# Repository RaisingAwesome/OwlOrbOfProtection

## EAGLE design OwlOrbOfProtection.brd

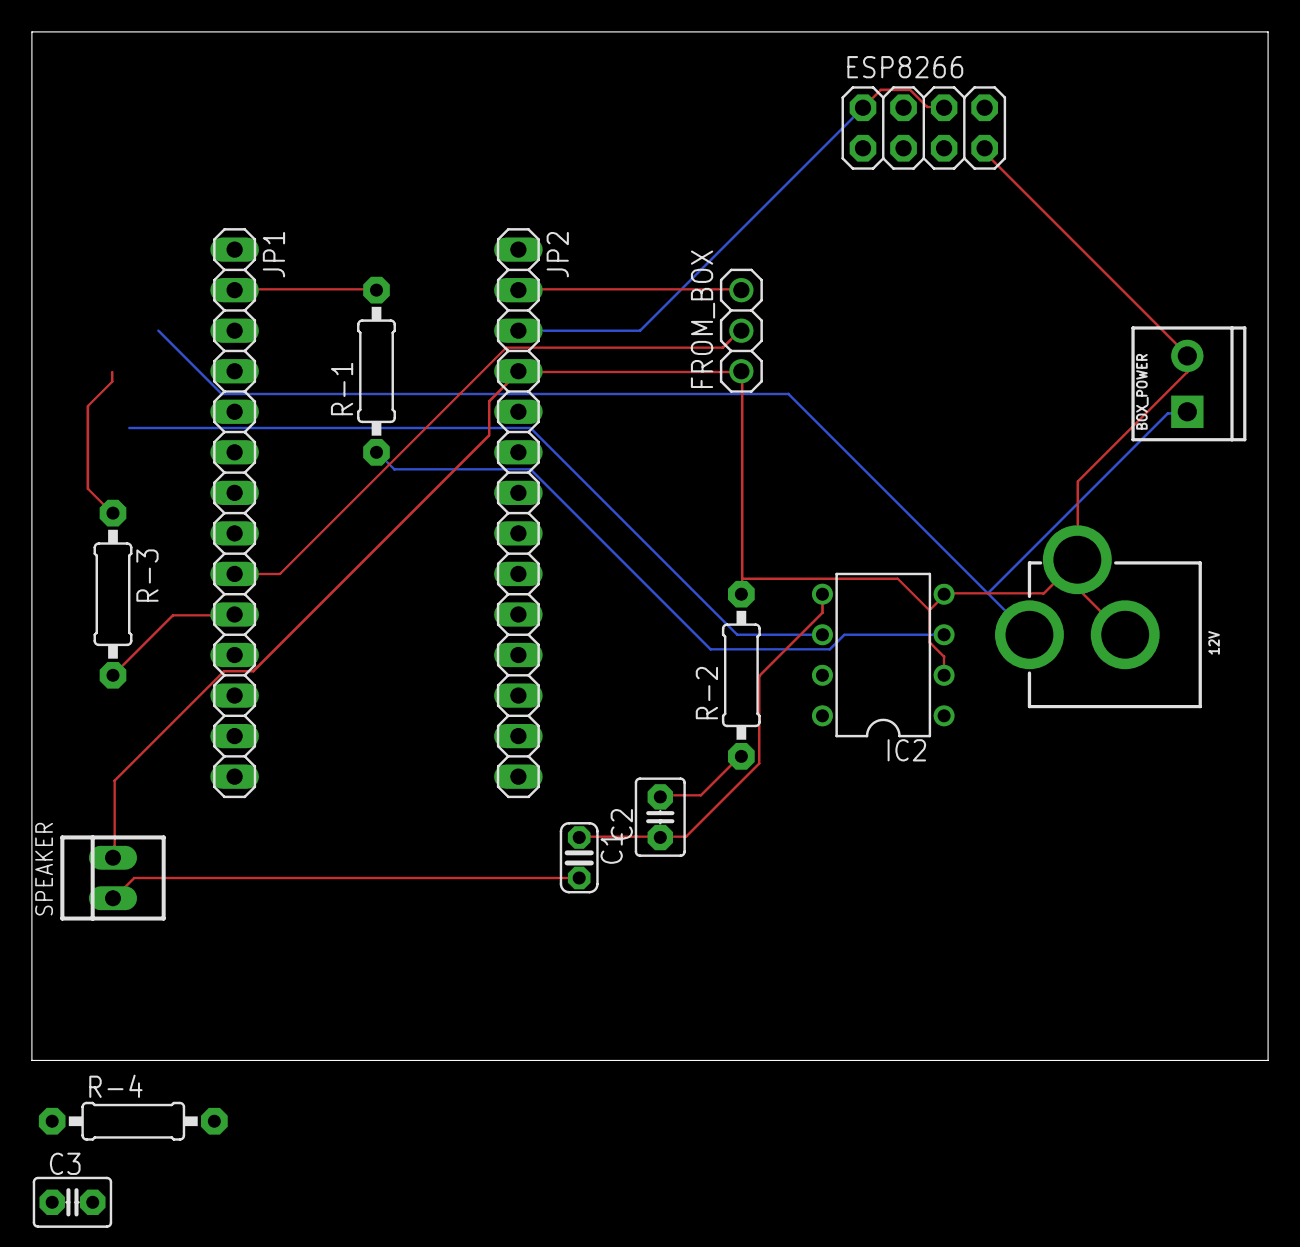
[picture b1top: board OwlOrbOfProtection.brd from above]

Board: 2 copper layers, 77.5 x 64.4 mm, 15 parts (0 on the bottom side), 13 nets.

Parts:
12V: POWER_JACK; POWER_JACK_PTH
BOX_POWER: SCREWTERMINAL-3.5MM-2
C1: 247uF; C025-024X044
C2: 0.1uF; C2.5-3
C3: 10uF; C2.5-3
ESP8266: 2X04
FROM_BOX: 1X03
IC2: LM386N-1; DIL08
JP1, JP2: 1X14
R-1, R-4: 4.7K; 0207/10
R-2: 10 ohm; 0207/10
R-3: 220 ohm; 0207/10
SPEAKER: 22-23-2021

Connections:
3.3V: ESP8266.2, ESP8266.6, JP2.3
5V: FROM_BOX.3, JP2.2
12V: 12V.PWR, BOX_POWER.1
GND: 12V.GND, 12V.GNDBREAK, BOX_POWER.2, ESP8266.7, FROM_BOX.1, IC2.2, IC2.4, JP2.4, R-2.2, R-4.1, SPEAKER.2
unnamed: FROM_BOX.2, JP1.9
unnamed: C2.2, R-2.1
unnamed: C1.1, C2.1, IC2.5
unnamed: ESP8266.5, R-3.1
unnamed: IC2.3, R-1.1, R-4.2
unnamed: C3.1, IC2.6, R-1.2
unnamed: C1.2, SPEAKER.1
unnamed: C3.2, JP1.2
unnamed: JP1.10, R-3.2

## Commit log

2020-07-15 OwlOrb.ino
    FIle Uploaded
2020-07-15 ESP8266.ino
    Uploaded File
2020-07-15 Eagle Files
    Uploaded
2020-07-15 Owl Base Fusion File

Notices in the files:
parts and their libraries:
SparkFun-Connectors: Licensing: Creative Commons ShareAlike 4.0 International - https://creativecommons.org/licenses/by-sa/4.0
